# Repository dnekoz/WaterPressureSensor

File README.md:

# WaterPressureSensor

Прошивка **3.1.1** для **Wemos D1 mini / ESP8266**. Измеряет давление по сигналу A0, показывает его на OLED SSD1306 и в локальном браузере, публикует MQTT и конфигурацию Home Assistant Discovery. Настройки, сертификат CA и обновление прошивки доступны через веб-интерфейс.

Измерения работают без MQTT и Wi-Fi. Истории показаний, управления насосом и аварийной автоматики нет. Индикатор корректного сигнала означает измеримость показания, а не безопасность давления в системе.

## Платформа и сборка

Версия прошивки, окружения и зависимости определены в [platformio.ini](platformio.ini).

| Компонент | Значение |
|---|---|
| Основное окружение | `d1_mini` |
| PlatformIO platform | `espressif8266@4.2.1` |
| Framework | Arduino Core 3.1.2, пакет `3.30102.0` |
| NON-OS SDK | Штатный 3.0.5; флаг `PIO_FRAMEWORK_ARDUINO_ESPRESSIF_SDK305` |
| Adafruit GFX / SSD1306 / BusIO | 1.12.6 / 2.5.17 / 1.17.4 |
| PubSubClient / ArduinoJson | 2.8 / 7.4.3 |
| Serial / файловая система | 115200 бод / LittleFS |

Установите PlatformIO Core или расширение PlatformIO для VS Code. Из корня проекта:

```sh
pio run -e d1_mini
pio run -e d1_mini -t upload --upload-port COM4
pio device monitor -p COM4 -b 115200
```

Замените `COM4` фактическим портом платы. Если `pio` отсутствует в PATH, используйте `python -m platformio` из Python-окружения с установленным PlatformIO.

Результат — `.pio/build/d1_mini/firmware.bin`. Скрипт `scripts/embed_web.py` сжимает HTML/CSS/JS из [web](web) и включает их в приложение как PROGMEM. **Загрузка файловой системы `uploadfs` для интерфейса не требуется.**

Окружение `d1_mini_diag` добавляет диагностику Wi-Fi и суффикс версии `-diag-sdk305`. Обычная сборка диагностический журнал не ведёт.

## Первый запуск

1. Откройте Serial 115200: там выводятся версия, SDK, сообщения Wi-Fi и строка `[portal] пароль интерфейса и точки доступа: …`.
2. Если сохранённой сети нет, подключитесь к `WaterSensor-xxxxxx`. Начальный пароль — **`water1234`**. Корректный ранее сохранённый пароль при обновлении не заменяется.
3. Откройте `http://192.168.4.1/`. На телефоне сохраните подключение, если система предупреждает об отсутствии интернета.
4. Нажмите значок замка и войдите с паролем интерфейса.
5. В разделе **Подключение** задайте сеть 2,4 ГГц и при необходимости MQTT/TLS.
6. В разделе **Калибровка** проверьте коэффициенты своего датчика и входной цепи.

При сохранённой сети сначала начинается подключение к ней; резервная AP предлагается через 15 секунд отсутствия связи. Она не обязана появляться немедленно при каждом старте.

После подключения к роутеру найдите STA-IP в Serial, DHCP-списке роутера или веб-интерфейсе. Имя `http://wps-xxxxxx.local/` работает при поддержке mDNS сетью и клиентом. `xxxxxx` — шестизначный chip ID. Рабочий OLED не показывает STA-IP; адрес на экране `SETUP MODE` относится к резервной AP.

### Доступ и пароли

Показания и статус доступны без входа. Настройки, поиск и смена Wi-Fi, загрузки, удаление CA и перезапуск требуют сессии. Сессия действует час с момента входа. Новый успешный вход заменяет предыдущую сессию; смена пароля интерфейса её аннулирует. Между попытками входа выдерживается минимум 3 секунды.

Открытие окна входа временно показывает пароль на OLED. Видимая вкладка с открытым окном продлевает показ каждые **20 секунд**. Вход, закрытие окна и переход вкладки в фон отправляют запрос скрытия. Если браузер закрыт, сеть потеряна или запрос не дошёл, через **60 секунд без продления** устройство возвращает обычный экран: показания либо `SETUP MODE` в зависимости от состояния AP. Отсутствие OLED не останавливает измерения.

Кнопки с глазом раскрывают только введённые значения. Сохранённые пароли MQTT и интерфейса API не возвращает. Явный выход очищает и скрывает введённые пароли.

Пароль интерфейса: **8–63 печатных ASCII-символа без пробелов**. Уже работающая AP сохраняет прежний пароль; следующая создаваемая AP использует текущее значение настроек. После перезапуска пароли интерфейса и AP совпадают. До перезапуска подсказка OLED может содержать новое значение: для ранее запущенной AP используйте прежний пароль.

Веб-интерфейс работает по **HTTP**; пароли хранятся во flash без шифрования. Используйте доверенную локальную сеть. TLS защищает соединение с MQTT-брокером, а не браузерный интерфейс.

## Интерфейс и OLED

| Раздел | Возможности |
|---|---|
| Обзор | Давление, измеримый диапазон, состояния датчика, Wi-Fi и MQTT, напряжение, АЦП, RSSI и память |
| Подключение | Поиск и сохранение Wi-Fi, MQTT, Discovery, TLS, загрузка и удаление CA |
| Калибровка | Четыре коэффициента и предварительный расчёт диапазона |
| Устройство | Идентификатор, версия, IP, время работы, имя, пароль, OTA и перезапуск |

Интерфейс адаптируется к телефону и компьютеру. Тема сначала следует системе, затем сохраняется в браузере. Ресурсы локальные; интернет и CDN не нужны.

Опрос статуса выполняется с паузой 2 секунды после предыдущего запроса, без параллельных запросов статуса. Он останавливается в скрытой вкладке и на время OTA. Через 5 секунд без свежего ответа манометр показывает «—». Загруженные черновики форм не перезаписываются фоновым опросом.

OLED: SSD1306 128×64, I²C-адрес `0x3C`, без отдельного RESET; используются стандартные выводы `Wire` выбранной платы. Настройки находятся в [Config.h](src/Config.h). При отсутствии ответа дисплея остальная прошивка продолжает работу.

Экран обновляется примерно каждые 250 мс. Рабочий режим показывает давление, `W:ok`/`W:--` и `M:off`/`M:ok`/`M:tls`/`M:--`. Ошибки обозначаются `NO SENSOR`, `OVER`, `STALE DATA`. Экран AP показывает SSID, пароль и адрес портала.

## Измерение и калибровка

Один отсчёт A0 берётся примерно каждые **20 мс**. Скользящее среднее использует **32 отсчёта**: номинальное окно 0,64 секунды. После первого отсчёта и паузы от 500 мс окно заполняется свежим значением. Пропущенные измерения не восстанавливаются.

Формулы из [Logic.cpp](src/Logic.cpp):

```text
V = raw / 1023 × adcFullScaleV
P, МПа = (V − vZero) × pFullMPa / (vFull − vZero)
P, бар = P, МПа × 10
Pmax, бар = (min(adcFullScaleV, vFull) − vZero) × pFullMPa / (vFull − vZero) × 10
```

`V` — восстановленное напряжение датчика до внешнего делителя. Настройка `adcFullScaleV` меняет пересчёт, но не допустимое физическое напряжение входа A0.

| Поле | По умолчанию | Пределы |
|---|---:|---|
| `adcFullScaleV` | 3,2 В | 1–10 В; напряжение датчика, соответствующее отсчёту 1023 |
| `vZero` | 0,5 В | Не меньше 0, строго ниже `adcFullScaleV` |
| `vFull` | 4,5 В | Не больше 10 В; `vFull − vZero > 0.1 В` |
| `pFullMPa` | 0,5 МПа | Больше 0, не больше 100 МПа |

Исходная расчётная граница — **3,375 бар**. Коэффициенты по умолчанию не подтверждают соответствие фактическому датчику: проверьте калибровку по опорному давлению. Небольшое отрицательное давление сохраняется.

- `over`: отдельный отсчёт достиг 1020 либо напряжение превысило `vFull + 0.05 В`.
- `fault`: отсчёт отрицательный, напряжение ниже `vZero − 0.2 В` или результат пересчёта неконечный. Флаг характеризует сигнал, не устанавливая однозначно причину неисправности.
- `stale`: выборки ещё нет либо возраст последнего отсчёта достиг 1000 мс.

Кратковременные нарушения проверяются до усреднения. `over` и `fault` снимаются после секунды устойчивого восстановления с гистерезисом; длинная пауза не считается восстановлением. Усреднённое значение также проверяется при чтении.

При любом из этих флагов давление в JSON равно `null`; напряжение и отсчёты остаются доступны. Сохранение настроек и изменение CA переприменяют MQTT и перезапускают фильтр через основной цикл.

## Wi-Fi

SSID: **1–32 байта**. Пароль: **8–63 байта** или пустая строка для открытой сети. Прежний пароль можно сохранить только для того же SSID.

Менеджер хранит копию SSID/пароля в RAM. Перед начальным подключением, сменой сети и принудительным повтором он очищает текущую конфигурацию SDK только в RAM, выключает STA, ждёт не менее **200 мс после фактического выключения** без `delay()`, затем включает STA с явными SSID/паролем, без фиксации канала и BSSID. Резервная AP и профиль во flash сохраняются.

Успех требует `WL_CONNECTED` и ненулевого IP. Если SDK не восстановил связь самостоятельно за 30 секунд, подготовка STA повторяется. Flash обновляется при применении сети с портала; обычные повторы используют RAM. После получения IP заново запускаются HTTP и mDNS.

AP предлагается после 15 секунд отсутствия связи. При сохранённой сети она закрывается через 180 секунд без клиентов. Без сохранённой сети этот таймаут не применяется. После подключения к роутеру AP закрывается без клиентов, когда с её запуска прошло больше 10 секунд. Закрытие AP не останавливает STA-повторы; новое окно настройки можно открыть перезапуском устройства.

## MQTT и Home Assistant

Пустой адрес брокера выключает MQTT. Client ID — `wps_xxxxxx`.

| Поле | Значение по умолчанию / ограничение |
|---|---|
| `mqttHost` | Пусто; DNS-имя или IPv4 без протокола и порта, до 63 байт |
| `mqttPort` | 1883; 1–65535 |
| `mqttUser` | Пусто; до 31 байта, пустое значение означает отсутствие аутентификации |
| `mqttPass` | Пусто; до 63 байт |
| `mqttBase` | `watersensor/wps_xxxxxx`; непустая строка до 63 байт |
| `mqttIntervalS` | 10 секунд; целое 1–3600 |
| `haPrefix` | `homeassistant`; до 31 байта, пусто выключает Discovery |
| `deviceName` | `Water Pressure`; непустая строка до 31 байта UTF-8 |

База и префикс не допускают `+`, `#`, управляющих символов и завершающего `/`. Строковые пределы считаются в байтах UTF-8.

Пустое поле пароля в браузерной форме сохраняет секрет; флажок удаления очищает его. В API отсутствие `mqttPass` сохраняет значение, явное `"mqttPass":""` удаляет.

```text
<mqttBase>/state                                  JSON, без retain
<mqttBase>/status                                 online/offline, retain
<haPrefix>/sensor/<deviceId>/<entity>/config        Discovery, retain
```

Брокеру задаётся Last Will `offline`. После подключения отправляются `online`, Discovery и свежие показания; далее состояние публикуется по `mqttIntervalS`. Публикации имеют QoS 0.

Discovery создаёт `pressure`, `voltage`, `rssi`, `raw` со сроком актуальности `3 × mqttIntervalS + 10` секунд. При смене префикса старые retained-конфигурации удаляются. Ошибки публикации или сохранения приводят к повтору через 10 секунд; прежний применённый префикс хранится до завершения операции. Успешный `publish()` не подтверждает хранение брокером. При смене брокера записи на старом брокере нужно удалить отдельно.

Первая попытка соединения выполняется сразу после появления Wi-Fi. После неудач пауза растёт до 30 секунд и отсчитывается от конца попытки. CONNACK 1, 2, 4 и 5 останавливают повторы до переприменения настроек; 3 и транспортные ошибки считаются временными. Serial сообщает этап, код, адрес, причину и действие, не печатая MQTT-пароль.

### TLS

| `mqttTlsMode` | Режим |
|---:|---|
| 0 | Незашифрованный TCP |
| 1 | TLS без проверки подлинности брокера |
| 2 | TLS с SHA-1 отпечатком сертификата |
| 3 | TLS с CA, проверкой имени и срока сертификата |

`mqttFingerprint`: 40 hex-символов либо 20 пар через двоеточия, без пробелов. Ошибочный отпечаток и неизвестный режим блокируют подключение без автоматического понижения защиты.

Для CA загрузите корневой PEM **1–4096 байт**, используйте имя брокера из сертификата и доступный сервер времени. `ntpServer` содержит до 63 байт; пусто означает `pool.ntp.org`. До установки часов режим CA ждёт NTP. Форма переключает стандартные порты 1883/8883 при смене TLS; нестандартный порт сохраняется.

Проба MFLN определяет запрошенный приёмный буфер: 1024 байта при положительном результате, иначе 16384. Передающий буфер — 512 байт. Проверяется крупнейший свободный блок: минимум 9000 или 23000 байт соответственно. Это не полный размер всех выделений BearSSL.

**Подключения MQTT/TLS синхронные.** DNS, TCP, MFLN и TLS могут приостанавливать HTTP, OLED и выборку. Константы таймаутов не задают гарантированную общую длительность. Регистрация коротких гидроударов не гарантируется.

## HTTP API

Базовый адрес — IP устройства, порт 80. JSON использует `Content-Type: application/json`. Все POST требуют `X-WPS-Request: 1`. Сессия передаётся cookie `wps_session` с `HttpOnly`, `SameSite=Strict` и сроком один час. CORS не включён.

| Метод и путь | Сессия | Назначение |
|---|---|---|
| `GET /reading` | Нет | Показания в формате MQTT |
| `GET /api/status` | Нет | Показания, соединения, версия, ошибки и состояние входа |
| `POST /api/login` | Нет | `{"password":"…"}`; создаёт cookie |
| `POST /api/login/display` | Нет | `{"visible":true}` продлевает показ OLED на 60 секунд, `false` скрывает |
| `POST /api/logout` | Да | Завершает сессию |
| `GET /api/settings` | Да | Настройки без секретов, `mqttPasswordSet`, `wifiSsid` |
| `POST /api/settings` | Да | Частичное транзакционное обновление |
| `POST /api/wifi` | Да | `ssid`, `password`, необязательный `keepPassword` |
| `POST /api/wifi/scan` | Да | Запуск поиска |
| `GET /api/wifi/scan` | Да | `running`, до 20 сетей с `ssid`, `rssi`, `secure` |
| `POST /api/ca` | Да | Multipart-файл; браузер использует поле `certificate` |
| `POST /api/ca/delete` | Да | Удаление CA и переприменение MQTT |
| `POST /api/firmware` | Да | Ровно один multipart-файл; поле браузера `firmware` |
| `POST /api/restart` | Да | Перезапуск после ответа |
| `GET /api/diagnostics/wifi` | Да | NDJSON; только диагностическая сборка |

Действия возвращают `message` либо `error`. Ошибки параметров дают 400, отсутствие сессии — 401, служебного заголовка — 403, частый вход — 429, ошибка сохранения настроек — 507. Невалидный patch не применяется частично. JSON ограничен 2048 байтами в обработчике; это не ограничивает предварительную буферизацию тела в ESP8266WebServer.

```json
{"bar":2.55,"mpa":0.255,"volt":2.540,"raw":812,"rssi":-58,"over":false,"fault":false,"heap":24568,"raw_instant":813,"age_ms":8,"stale":false}
```

`raw` — средний отсчёт, `raw_instant` — последний, `volt` — напряжение датчика до внешнего делителя, `age_ms` — возраст выборки, `heap` — свободные байты памяти. `/api/status` помещает объект в `reading` и дополнительно возвращает `max_bar`, `heap_block`, `storage_error`, `tls_error`, состояния соединений и `login_password_visible`. Последнее поле означает временный режим показа, не подтверждая наличие OLED. `uptime_s` основан на `millis()` и обнуляется также при его переполнении примерно через 49,7 суток.

API настроек допускает поля из таблиц MQTT, TLS и калибровки, а также `portalPass`. Внутренний `haPrefixApplied` изменять нельзя. Отсутствующие поля patch остаются прежними; неизвестные поля, неверные типы, превышение длины и неконечные коэффициенты отвергаются.

## Постоянное хранение

LittleFS хранит `/config.json` и CA `/ca.pem`. Временные файлы — `/config.tmp` и `/ca.tmp`. Профиль Wi-Fi хранится отдельно средствами SDK.

Настройки сначала сериализуются во временный файл. Проверяются ожидаемый и фактический размеры, разбор JSON и точное совпадение записанных байтов; затем выполняется `rename`. RAM-настройки заменяются только после успешного сохранения. При загрузке старых файлов отсутствующие поля сохраняют значения по умолчанию. Некорректные коэффициенты исправляются, а ошибки TLS не превращаются автоматически в небезопасный режим.

CA проверяется по размеру и разбирается BearSSL до замены. Ошибки записи, отмена, неверный сертификат и ошибка переименования сохраняют прежний CA.

Существующая LittleFS при ошибке монтирования автоматически не форматируется. Форматирование допускается только для полностью стёртого раздела. При недоступном хранилище прошивка использует временные настройки и сообщает ошибку.

## OTA из браузера

1. Соберите `pio run -e d1_mini`.
2. Войдите и откройте **Устройство → Обновление прошивки**.
3. Выберите `.pio/build/d1_mini/firmware.bin`, подтвердите загрузку и дождитесь ответа.
4. После восстановления связи проверьте версию. Если ответ потерялся, проверьте её перед повторной загрузкой.

Принимается обычный несжатый BIN данного проекта, созданный `elf2bin.py` закреплённого Core 3.1.2. Gzip, пустой файл, несколько файлов в запросе, неверный заголовок, лишние байты, усечённый образ и неверная CRC32 отвергаются.

Проверка потоковая, с постоянным расходом RAM: сверяются заголовки, встроенная полная длина и CRC32 всего полученного образа. При расчёте CRC поля размера/CRC считаются восемью нулевыми байтами согласно формату Core. Дополнительный манифест не нужен. CRC обнаруживает повреждение, но **не является цифровой подписью** и не подтверждает автора прошивки.

Запись идёт в свободную область OTA. Команда установки Updater создаётся только после проверки полного образа и повторной проверки сессии. При отмене, ошибке и истечении сессии Updater явно закрывается без установки с освобождением буфера. Один байт ёмкости резервируется, чтобы отмена не могла подтвердить полностью заполненное обновление. Во время установки не отключайте питание.

Обычная USB-загрузка и OTA с прежней разметкой flash сохраняют настройки и CA. Полное стирание flash и загрузка файловой системы их не сохраняют.

## Ограничения текущей реализации

- Синхронные сетевые операции нарушают регулярность выборки и обновления экрана. Жёсткой гарантии периодов 20/250 мс нет.
- В Core 3.1.2 `setTimeout()` используемой TLS-обёртки не меняет TCP-таймаут внутреннего контекста. Значение 3000 мс из конфигурации не является фактическим пределом этого этапа TLS.
- Отрицательная MFLN-проба кэшируется до переприменения настроек. После временного сбоя пробы при нехватке большого непрерывного блока для новой пробы потребуется сохранить настройки или перезапустить устройство.
- Штатное отключение MQTT не публикует отдельный `offline`; прежний retained-статус может остаться `online`. В HA актуальность показаний дополнительно ограничена `expire_after`.
- Уже работающая AP не меняет пароль при сохранении нового. Для однозначного применения и достоверной подсказки AP перезапустите устройство.
- Точность датчика, радиосвязь и восстановление после перезапуска конкретного роутера требуют стендовых проверок. Native-тесты этого не подтверждают.

## Разработка и проверки

| Путь | Назначение |
|---|---|
| `src/main.cpp` | Инициализация и основной цикл |
| `src/Logic.*`, `src/Sensor.*` | Формулы, фильтр, валидация, JSON, Discovery и чтение A0 |
| `src/Settings.*`, `src/CaStore.*` | Постоянное хранилище |
| `src/WifiConnection.*`, `src/Mqtt.*` | STA, MQTT/TLS и повторы |
| `src/Portal.*` | HTTP, сессии, AP, загрузки и применение настроек |
| `src/FirmwareImage.h`, `src/FirmwareUpload.*` | Проверка BIN и жизненный цикл OTA |
| `src/LoginDisplay.h`, `src/Display.*` | Срок показа пароля и OLED |
| `src/WifiDiagnostics.*` | Условно компилируемый журнал Wi-Fi |
| `web/`, `scripts/`, `test/` | Интерфейс, инструменты и native-тесты |

```sh
pio test -e native
pio run -e d1_mini -e d1_mini_diag
python scripts/verify_nonos_sdk.py
python scripts/verify_nonos_sdk.py --environment d1_mini_diag
```

Native-сборка компилирует `Logic.cpp`; отдельные тесты дополнительно включают производственные модули хранения, Wi-Fi и OTA с заглушками. Покрыты ошибки записи, транзакционность, переполнение `millis()`, повреждение/отмена OTA, освобождение буфера и срок показа пароля. CA-заглушка не проверяет криптографическую корректность PEM; заглушки Updater и Wi-Fi не заменяют испытания flash и радио.

`verify_nonos_sdk.py` читает готовые ELF/BIN/map, проверяя реальный `SDK_VERSION` и происхождение 11 SDK-архивов. CI запускает native-тесты, обе сборки и обе проверки SDK.

### Предпросмотр и браузерный тест

```sh
python scripts/preview.py
```

Откройте `http://127.0.0.1:8765/`, пароль **`preview-access123`**. Сервер явно показывает тестовые данные и не управляет платой. Другой порт задаётся `--port`.

Для smoke-теста нужны Node.js, Google Chrome и доступный модуль `playwright`:

```sh
node scripts/ui_smoke.cjs
```

По умолчанию используется предпросмотр на порту 8765; другой адрес — `WPS_PREVIEW_URL`. Проверяются четыре раздела, обе темы, пять ширин, формы, парольный интерфейс и восстановление отображения. Скриншоты сохраняются в `.pio/ui-review/`. Продление показа пароля проверяется с управляемыми часами браузера.

### Диагностика Wi-Fi

```sh
pio run -e d1_mini_diag
python scripts/capture_wifi_diagnostics.py --url http://DEVICE_IP --duration 900
```

Команда сборки не устанавливает диагностический образ на устройство. Сборщик запрашивает пароль без отображения, читает статус и журнал; его результаты сохраняются в `.pio/hardware/wifi-diagnostics-*`. Подробности: [WIFI_DIAGNOSTICS.md](docs/WIFI_DIAGNOSTICS.md), [NONOS_SDK_3.0.5.md](docs/NONOS_SDK_3.0.5.md).

Документы [docs](docs) содержат исторические испытания 3.0.x и 3.1. Их результаты, хеши и ограничения относятся к указанным версиям и не переносятся автоматически на 3.1.1.

## Лицензия

Текст GNU GPL v3 находится в [LICENSE](LICENSE).

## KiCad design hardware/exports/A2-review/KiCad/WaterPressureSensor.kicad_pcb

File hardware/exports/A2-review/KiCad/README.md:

# WaterPressureSensor — аппаратная часть

Состояние: **A2, плата разведена и проверена в KiCad; выпуск для изготовления
ожидает сверки механики с реальными модулями**.

Плата **46 × 65 мм**, толщина 1,6 мм, одна физическая сторона меди **B.Cu**.
Все шесть цепей разведены дорожками 0,4 мм, зазор 0,25 мм; переходных отверстий
и проволочных перемычек нет. Предварительно принята медь 35 мкм.

## Зафиксированные требования

- KiCad 10.0.6; плата-носитель готовых модулей WeMos D1 Mini **USB Type-C** и SSD1306.
- Питание только через USB-разъём WeMos. Отдельный вход питания отсутствует.
- Датчик подключается через **RJ-10, 4P4C, гнездо для монтажа на плату**.
  Кабель датчика уже собран; пользователь задал контакты 1, 2 и 4.
- Сигнал датчика подключается непосредственно к A0. Внешнего делителя,
  фильтра и иных элементов согласования в этой версии нет.
- Одна сторона меди: B.Cu. Компоненты и разъёмы — с верхней стороны.
- OLED находится **вторым ярусом поверх WeMos**, подключается к высокому
  разъёму 1×4 «мама», установленному рядом с WeMos. Это последнее явное
  уточнение пользователя; вариант с двумя модулями рядом отменён.
- Нужно сохранить доступ к USB и кнопке Reset, проверить зазор по высоте,
  область антенны и возможность разборки.

## Соединения, подтверждённые прошивкой

| Сеть | Вывод WeMos | GPIO | Номер в символе U1 | Назначение |
|---|---|---|---|---|
| SENSOR_SIG | A0 | ADC | 2 | Сигнал датчика, без внешнего согласования |
| I2C_SDA | D2 | 4 | 13 | OLED SDA |
| I2C_SCL | D1 | 5 | 14 | OLED SCL |
| +3V3 | 3V3 | — | 8 | Выход встроенного стабилизатора |
| +5V_USB | 5V | — | 9 | Питание от USB WeMos |
| GND | GND | — | 10 | Общая земля |

Источники: `src/Config.h`, `src/Display.cpp`, файл варианта `d1_mini/pins_arduino.h`
из установленного ESP8266 Arduino Core 3.1.2. Назначения совпадают с README
прошивки. OLED RESET не подключается; `OLED_RESET = -1`.

Номера контактов U1 относятся к локальной копии стандартного символа
KiCad `RF_Module:WEMOS_D1_mini`. Это не нумерация GPIO.

## Распиновка датчика RJ-10, заданная пользователем

| Контакт J2 | Сеть | Соединение |
|---|---|---|
| 1 | +5V_USB | Вывод 5V WeMos, питание от его USB |
| 2 | GND | Общая земля |
| 3 | Резерв | Не подключается на плате-носителе, отмечен NC |
| 4 | SENSOR_SIG | Непосредственно A0 WeMos |

Эти соединения внесены в редактируемую схему и проверяются по экспортированному
netlist. При назначении посадочного места нумерацию его выводов необходимо
сверить с чертежом конкретного гнезда, включая вид со стороны пайки.
Контакт 3 принят как неиспользуемый на плате: пользователь назначил только
контакты 1, 2 и 4. Это допущение записано отдельно в `design.json`.

## Подключение OLED

Порядок контактов **при виде на лицевую сторону дисплея, слева направо**
задан пользователем. В схеме используются физические номера 1–4:

| Контакт J1 | Назначение OLED | Соединение с WeMos |
|---|---|---|
| 1, крайний слева | GND | GND |
| 2 | VCC | 3V3 |
| 3 | SCL | D1 / GPIO5 |
| 4, крайний справа | SDA | D2 / GPIO4 |

В [предоставленной карточке модуля](https://www.datasheethub.com/ssd1306-128x64-mono-0-96-inch-i2c-oled-display/)
указаны питание 3–5 В и габариты модуля 27 × 27 × 3,5 мм. Для проекта выбрано
питание OLED **3,3 В от WeMos**: таким образом подтяжки линий I²C к питанию
OLED находятся в домене 3,3 В ESP8266. Внешний источник питания не добавлен.

Карточка описывает типовой модуль, без конкретного артикула производителя.
Приложенный PDF — документация микросхемы SSD1306, а не размерный чертёж
четырёхконтактной платы дисплея. Поэтому 27 × 27 × 3,5 мм пока служат габаритной
оценкой: шаг контактов, смещение ряда относительно края, отверстия и высоту
сочленённого высокого разъёма ещё необходимо проверить. Номера 1–4 при
монтаже нельзя зеркально переносить с вида со стороны пайки.

## Конструкция платы A2

- WeMos повёрнут USB-разъёмом вправо. Принята стандартная посадка D1 Mini:
  два ряда по восемь контактов, шаг 2,54 мм, расстояние между рядами 22,86 мм.
  Type-C подтверждён пользователем; это ещё не подтверждает точную ревизию
  модуля или механическую идентичность конкретного клона.
- OLED находится над WeMos со смещением вправо от области антенны. Высокий
  разъём J1 расположен выше корпуса WeMos в плане, крайний левый контакт — GND.
  На Dwgs.User показан габарит OLED 27 × 27 мм. Приняты шаг контактов 2,54 мм
  и расстояние от ряда до края OLED 2 мм; эти два размера пока являются допущениями.
- Для J1 выбран **Samtec ESW-104-44-G-S**, корпус высотой **18,67 мм**.
  Высота корпуса не равна окончательному зазору между платами: проверьте
  фактическое сочленение с гребёнкой OLED, высоту WeMos на двух гнёздах 1×8
  и компоненты на нижней стороне OLED. Обычное гнездо с длинными выводами
  не обязательно обеспечивает такую же высоту над платой.
- J2 использует стандартный символ KiCad `Connector:4P4C` с четырьмя
  контактами 1–4. Контакты 1, 2 и 4 соединены согласно таблице выше.
  Для корпуса выбран футпринт семейства **EVERCOM 5301-4P4C / 5301-440xxx**.
  Его исходное имя в библиотеке KiCad — `RJ9_Evercom_5301-440xxx_Horizontal`:
  это четырёхконтактный корпус, используемый под обозначениями RJ9/RJ10.
  Контакт 3 оставлен резервным, без соединения. Другие RJ-10 не гарантируют
  совпадение отверстий и фиксаторов с этим семейством.
- Добавлены четыре отверстия 3,2 мм под крепёж M3. Отверстия крепления самого
  OLED не сверлятся: их размерный чертёж пока отсутствует. При необходимости
  механическую опору свободного края OLED следует согласовать с корпусом.
- Область запрета меди антенны из исходного футпринта WeMos сохранена.
  Разводка через неё не проходит. Характеристики Wi-Fi требуют проверки
  на собранном прототипе с установленным дисплеем и корпусом.
- Флаги питания обозначают существующий источник внутри WeMos/USB;
  это не дополнительные детали на плате.

## Проверки механики перед изготовлением

1. Наложить реальный Type-C WeMos на `review/fit-check-1to1.pdf`, проверить
   оба ряда контактов, ориентацию, доступ к USB и Reset. Печать — 100%,
   без масштабирования; расстояние между контрольными рисками должно быть 10 мм.
2. Размерный чертёж посадки OLED: шаг контактов, положение их центров
   относительно края, крепления и высота высокого разъёма. Порядок выводов
   и питание уже внесены; габаритная оценка модуля — 27 × 27 × 3,5 мм.
3. Сверить артикул и чертёж реального RJ-10 с выбранным семейством EVERCOM:
   четыре контакта, два пластиковых фиксатора и нумерацию со стороны пайки.
   Распиновка контактов 1, 2 и 4 уже подтверждена пользователем;
   контакт 3 не используется на плате.
4. Модель датчика, его питание, ток и диапазон сигнала. Для прямого входа
   следует проверить совместимость с A0 конкретного WeMos; текущая калибровка
   прошивки 0,5–4,5 В сама по себе её не подтверждает.
5. Ограничения корпуса/креплений и способ изготовления однослойной платы.

Посадочные места, контур и трассировка уже созданы. Gerber и сверловка
экспортированы как **A2-review**, не как проверенный выпуск в производство.
Точные размеры реальных модулей, 3D-зазоры и паспорт датчика программными
проверками не подтверждены.

KiCad использует минимальный двухслойный стек и нормализует сквозные площадки
как `*.Cu`. Это особенность CAD-исходника: **в пакет выведен только B.Cu**,
файл F.Cu отсутствует. Для изготовления нужна одна сторона меди. Все паяные
соединения доступны снизу, металлизация отверстий для электрической связности
не нужна. В Excellon объединены 30 отверстий: 24 контактных и 6 механических;
отчёт сохраняет их исходные категории PTH/NPTH из KiCad.

## Файлы и воспроизведение

- `WaterPressureSensor.kicad_pro` — проект KiCad.
- `WaterPressureSensor.kicad_sch` — редактируемая логическая схема.
- `WaterPressureSensor.kicad_pcb` — разведённая плата.
- `WaterPressureSensor.kicad_sym`, `sym-lib-table` — локальные символы.
- `WaterPressureSensor.pretty/`, `fp-lib-table` — локальные посадочные места.
- `design.json` — требования, сети и незаполненные аппаратные параметры.
- `tools/build_schematic.py` — воспроизводимое построение логической схемы.
- `tools/check_netlist.py` — сверка экспортированного netlist с таблицей сетей.
- `tools/build_board.py` — построение платы и маршрутизация только B.Cu.
- `tools/check_board.py` — проверка платы, связности, слоя и экспортного пакета.
- `tools/export_review.ps1` — ERC/DRC, экспорт и упаковка.
- `exports/WaterPressureSensor-A2-review.zip` — Gerber, сверловка, BOM,
  STEP носителя, исходники KiCad и материалы проверки. Не выпуск в производство.
- `review/` — экспорт схемы, netlist и отчёт ERC; это материалы проверки,
  шаблон 1:1 и изображения платы.

Первичная генерация требует установленной библиотеки KiCad; для открытия
готовой схемы используются локальные и встроенные в схему символы.

```powershell
& 'C:\Program Files\KiCad\10.0\bin\python.exe' hardware/tools/build_schematic.py
& 'C:\Program Files\KiCad\10.0\bin\kicad-cli.exe' sch erc --exit-code-violations --format json --output hardware/review/erc.json hardware/WaterPressureSensor.kicad_sch
```

Генератор не перезаписывает существующую схему без явного `--overwrite`.
Не запускайте перегенерацию поверх несохранённых правок редактора.

## Проверка A2

KiCad открыл схему и экспортировал PDF и XML netlist. Соединения U1, RJ-10
и всех четырёх физических контактов OLED сверены по netlist; PDF отрендерен
и просмотрен. Сверка схемы включает 25 проверок подключения и назначения GPIO.

**ERC пройден: 0 ошибок, 0 предупреждений**, проверка запущена с
`--exit-code-violations`; исключения нарушений не добавлялись. Контакт 3
RJ-10 и неиспользуемые контакты WeMos отмечены NC по назначению схемы.
**DRC пройден: 0 нарушений, 0 разрывов, 0 расхождений со схемой.**
Проверка запущена с `--schematic-parity --exit-code-violations`.
Копии всех трёх электронных посадочных мест совпадают с локальной библиотекой.
Исключения нарушений не добавлялись.

Аудит платы и экспортов включает 37 проверок: 24 электрических контакта,
52 сегмента общей длиной около 215,8 мм, только B.Cu, отсутствие переходных
отверстий, порядок контактов OLED, чистые отчёты ERC/DRC и единственный
медный Gerber. Проверены содержимое архива и отчёт 30 сверлений.

Осмотрены растровые экспорты схемы, посадки, меди и 3D-вид носителя.
STEP и 3D-вид содержат **только плату-носитель**: точные модели Type-C WeMos,
OLED, высокого разъёма и RJ-10 не представлены. Это не полная проверка сборки.

После сборки прототипа нужны измерение питания OLED/датчика и входа A0,
калибровка по эталонному давлению, проверка Wi-Fi с установленным экраном,
доступа к USB и отсутствия касания плат/компонентов.

Для повторного экспорта уже отредактированных исходников:

```powershell
& .\hardware\tools\export_review.ps1
# Либо из папки hardware / KiCad в распакованном архиве:
& .\tools\export_review.ps1
```

Скрипт экспорта не перестраивает и не перетрассирует плату. Генератор
`build_board.py` перезаписывает существующую плату только с `--overwrite`.

## Справочные источники

- [WeMos D1 mini: характеристики и чертежи](https://www.wemos.cc/en/latest/d1/d1_mini.html).
- [Схема D1 mini V4](https://www.wemos.cc/en/latest/_static/files/sch_d1_mini_v4.0.0.pdf).
- [Размерный чертёж D1 mini V4](https://www.wemos.cc/en/latest/_static/files/dim_d1_mini_v4.0.0.pdf).
- [Карточка OLED, предоставленная пользователем](https://www.datasheethub.com/ssd1306-128x64-mono-0-96-inch-i2c-oled-display/).
- [SSD1306: документация микросхемы](https://www.datasheethub.com/uploads/2022/08/ssd1306.pdf).
- Библиотека KiCad 10.0.6: `RF_Module:WEMOS_D1_mini` (символ).
- [Samtec ESW/ESQ: каталог с размерами корпуса](https://suddendocs.samtec.com/catalog_english/esw_th.pdf).
- Библиотека KiCad 10.0.6: `RF_Module:WEMOS_D1_mini_light` и
  `Connector_RJ:RJ9_Evercom_5301-440xxx_Horizontal` (исходные футпринты).

Ревизия V4 приведена как справочная, а не как подтверждение версии модуля
пользователя. Питание и механика реальных модулей ещё не проверены.

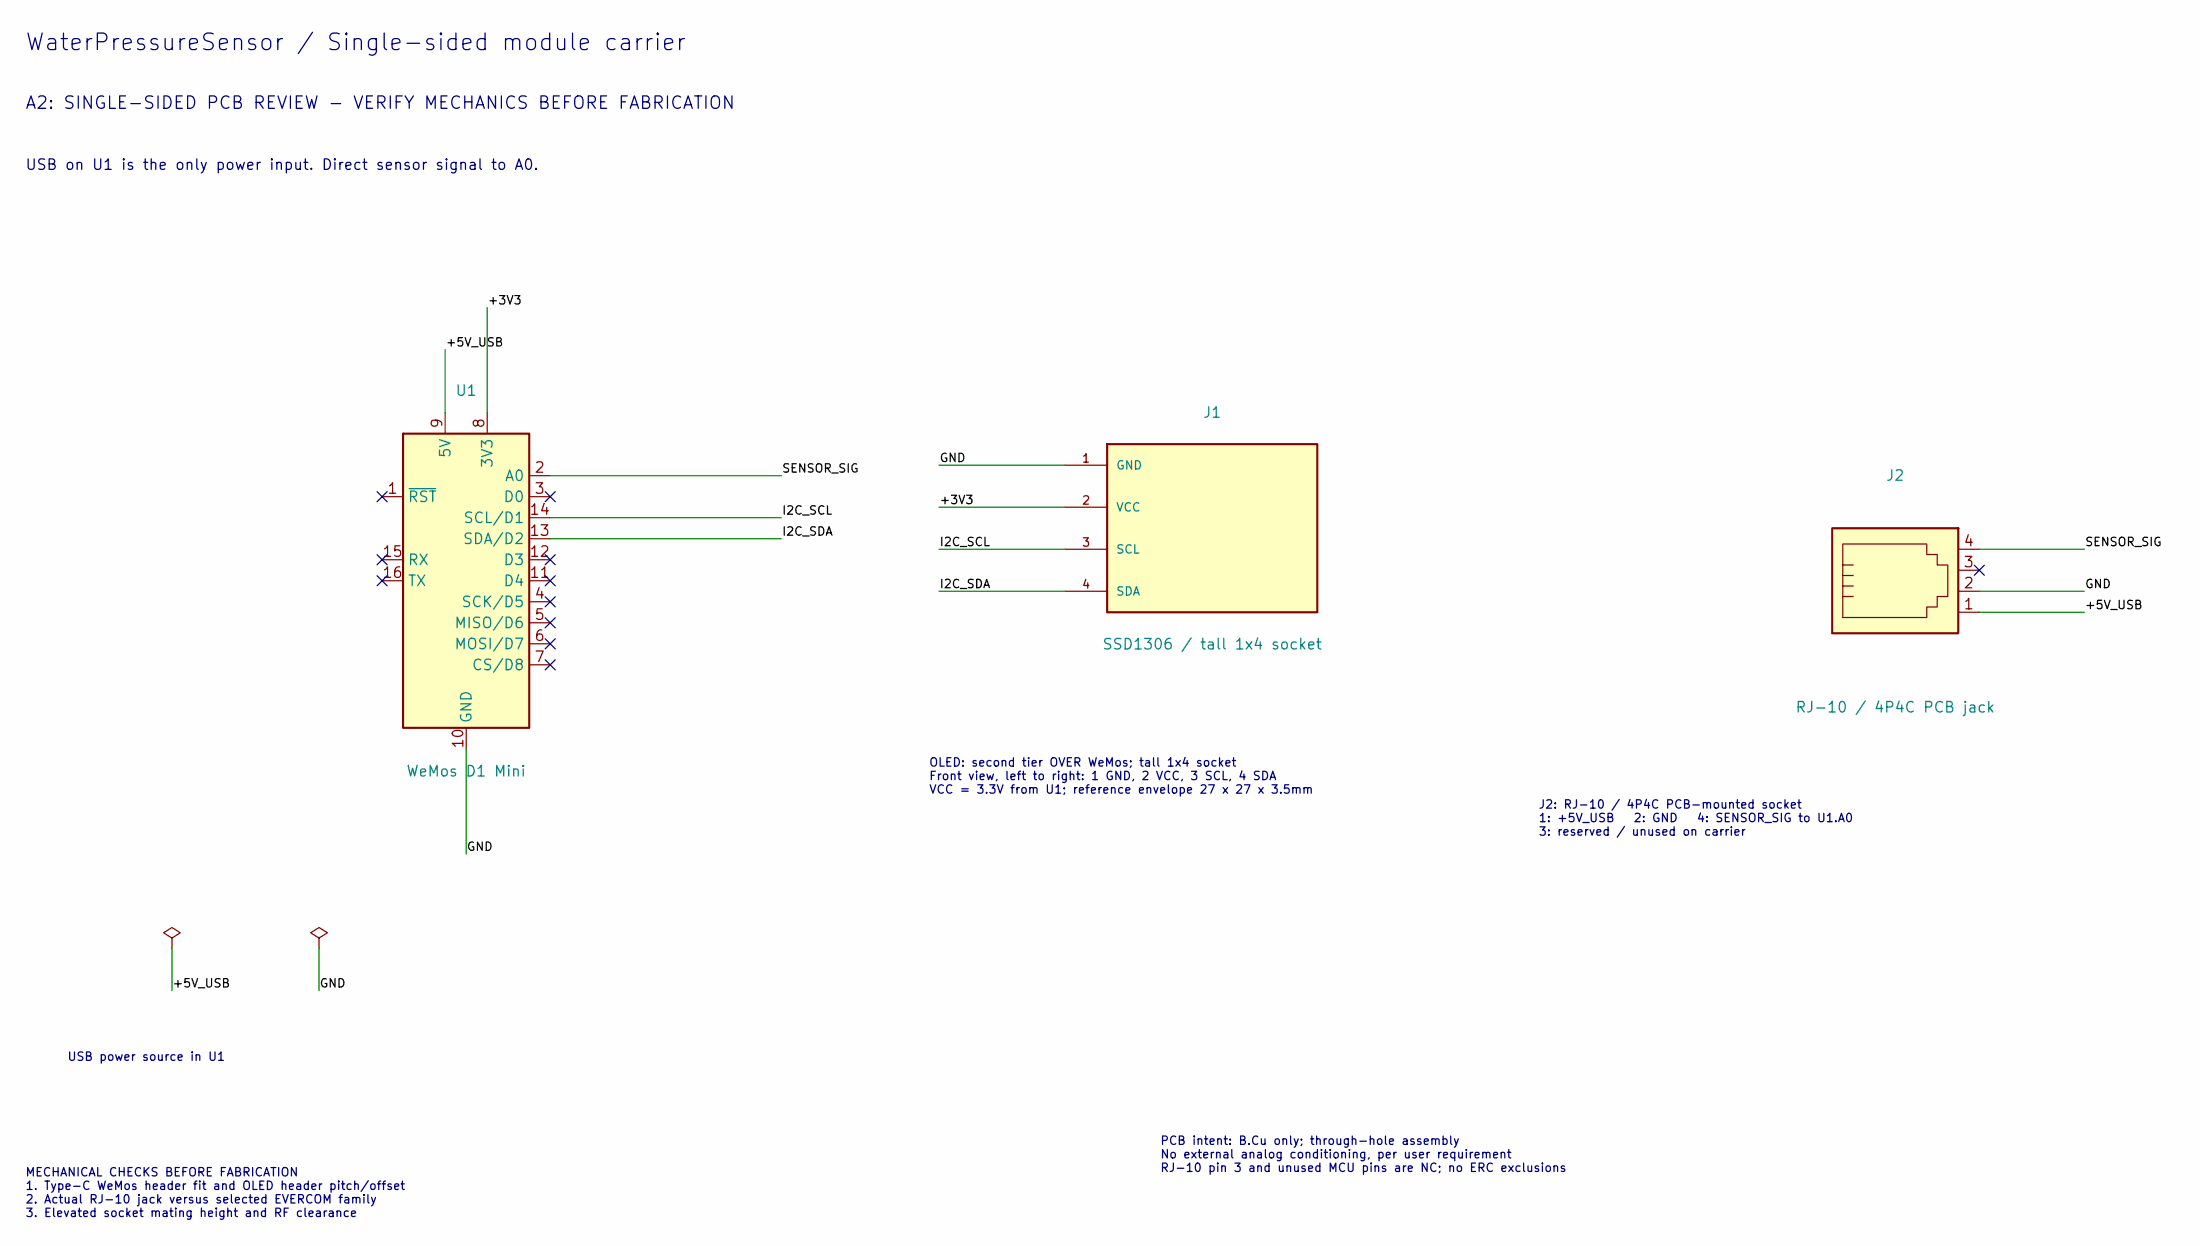
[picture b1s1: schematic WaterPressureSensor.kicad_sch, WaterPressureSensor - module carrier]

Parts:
J1: SSD1306 / tall 1x4 socket; OLED_ESW_1x04_P2.54_H18.67
J2: RJ-10 / 4P4C PCB jack; RJ10_Evercom_5301_4P4C
U1: WeMos D1 Mini; WEMOS_D1_mini_TypeC_headers

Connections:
/+3V3: J1.2 (VCC), U1.8 (3V3)
/+5V_USB: J2.1, U1.9 (5V)
/GND: J1.1 (GND), J2.2, U1.10 (GND)
/I2C_SCL: J1.3 (SCL), U1.14 (SCL/D1)
/I2C_SDA: J1.4 (SDA), U1.13 (SDA/D2)
/SENSOR_SIG: J2.4, U1.2 (A0)

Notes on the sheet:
WaterPressureSensor / Single-sided module carrier
A2: SINGLE-SIDED PCB REVIEW - VERIFY MECHANICS BEFORE FABRICATION
USB on U1 is the only power input. Direct sensor signal to A0.
USB power source in U1
OLED: second tier OVER WeMos; tall 1x4 socket Front view, left to right: 1 GND, 2 VCC, 3 SCL, 4 SDA VCC = 3.3V from U1; reference envelope 27 x 27 x 3.5mm
J2: RJ-10 / 4P4C PCB-mounted socket 1: +5V_USB 2: GND 4: SENSOR_SIG to U1.A0 3: reserved / unused on carrier
MECHANICAL CHECKS BEFORE FABRICATION 1. Type-C WeMos header fit and OLED header pitch/offset 2. Actual RJ-10 jack versus selected EVERCOM family 3. Elevated socket mating height and RF clearance
PCB intent: B.Cu only; through-hole assembly No external analog conditioning, per user requirement RJ-10 pin 3 and unused MCU pins are NC; no ERC exclusions

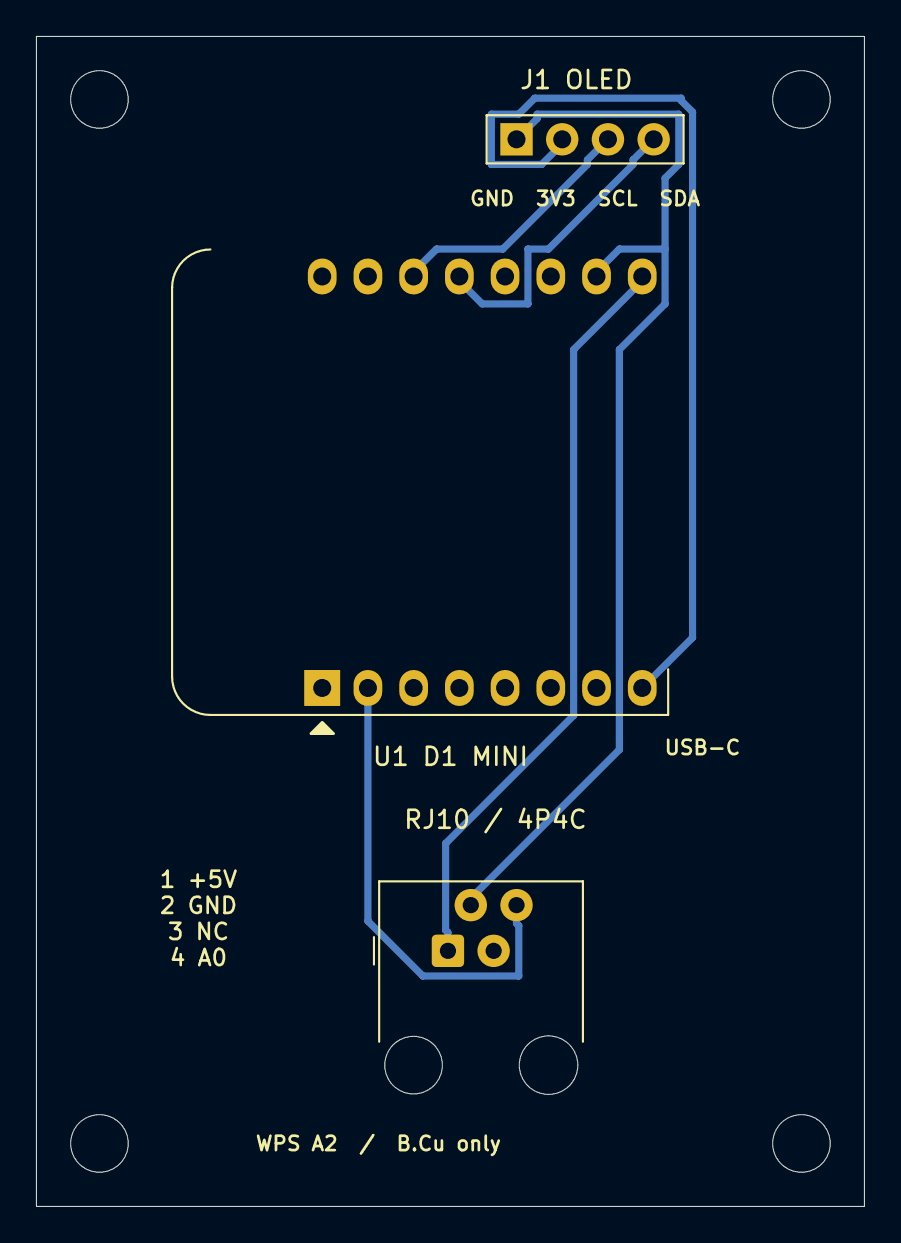
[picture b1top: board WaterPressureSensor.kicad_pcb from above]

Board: 2 copper layers, 46.0 x 65.0 mm, 7 parts (0 on the bottom side), 6 nets.

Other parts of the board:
H1, H2, H3, H4: MountingHole_3.2mm_M3
